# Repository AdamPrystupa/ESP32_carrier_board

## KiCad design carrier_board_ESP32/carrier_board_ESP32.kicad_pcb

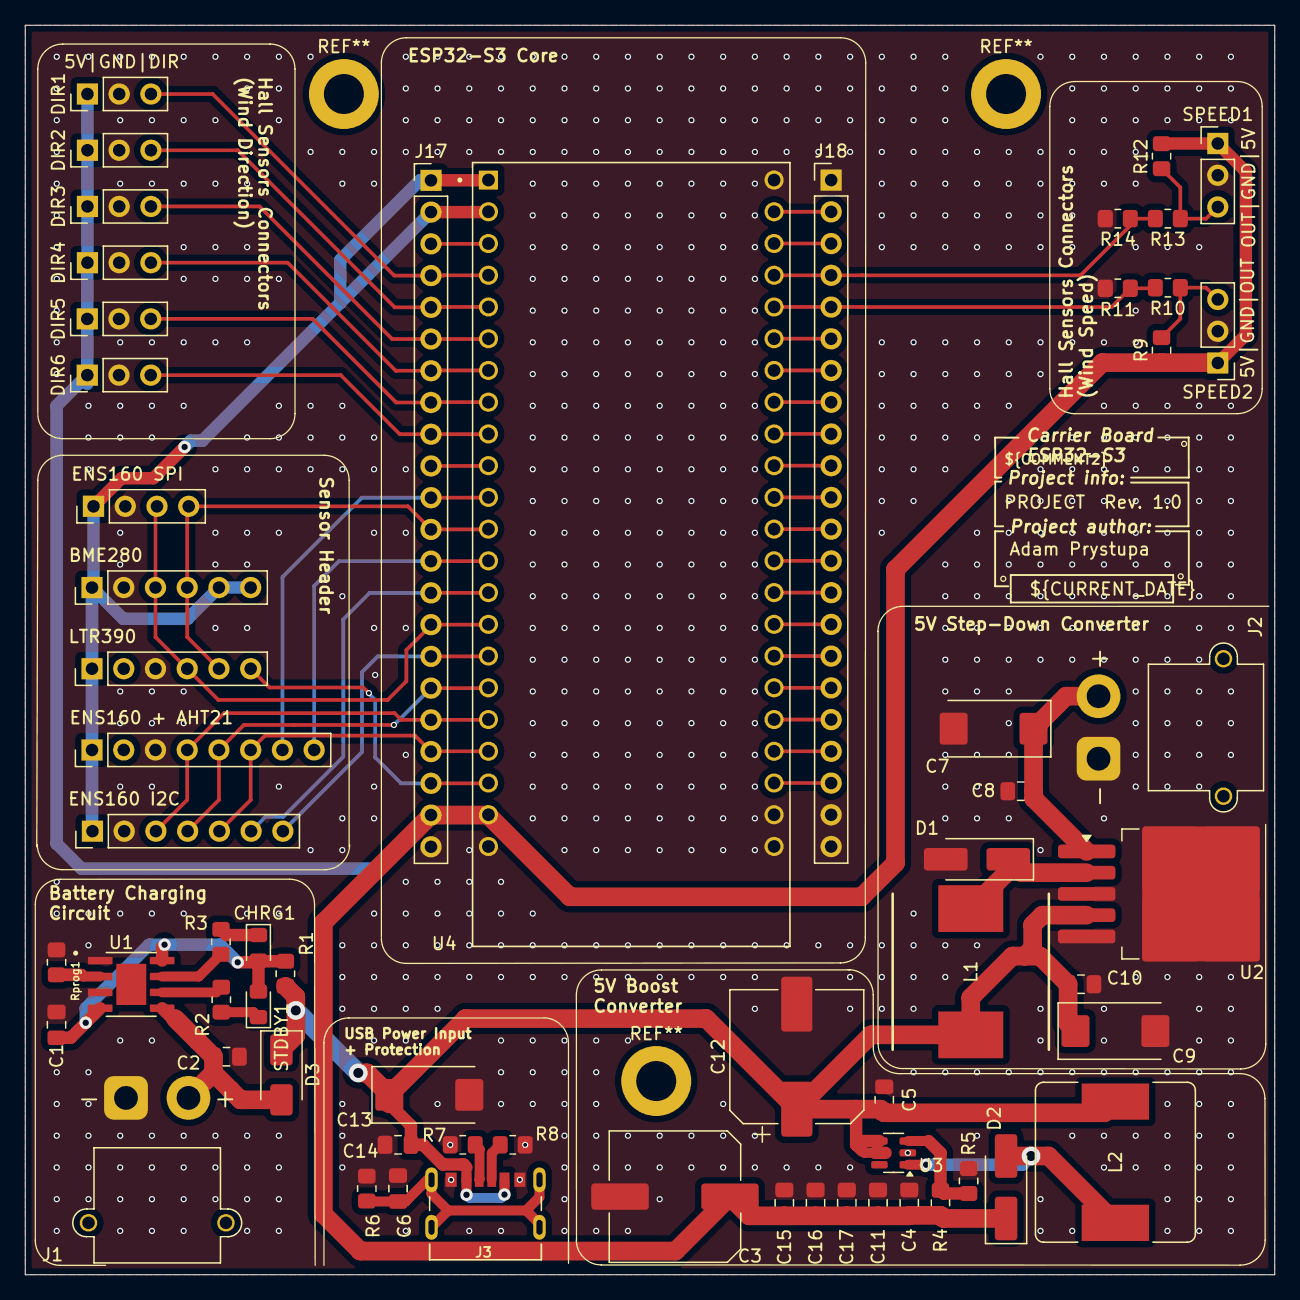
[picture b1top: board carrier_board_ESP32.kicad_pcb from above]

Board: 4 copper layers, 100.0 x 100.0 mm, 61 parts (0 on the bottom side), 57 nets.

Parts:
C1, C2, C8, C10, C15, C16, C17: 10uF; C_0805_2012Metric_Pad1.18x1.45mm_HandSolder
C3: 1000uF; C_Elec_10x10.2
C4, C5: 22nF; C_0805_2012Metric_Pad1.18x1.45mm_HandSolder
C6: 100nF; C_0805_2012Metric_Pad1.18x1.45mm_HandSolder
C7, C9: 100uF; CP_EIA-7343-15_Kemet-W_Pad2.25x2.55mm_HandSolder
C11: 47uF; C_0805_2012Metric_Pad1.18x1.45mm_HandSolder
C12: 2200uF; CP_Elec_10x10.5
C13: 10uF; CP_EIA-7343-15_Kemet-W_Pad2.25x2.55mm_HandSolder
C14: 1uF; C_0805_2012Metric_Pad1.18x1.45mm_HandSolder
CHRG1: RED; LED_0805_2012Metric_Pad1.15x1.40mm_HandSolder
D1, D2: DO-214AC; D_SMA_Handsoldering
D3: D; D_SMA
DIR1, DIR2, DIR3, DIR4, DIR5, DIR6: Conn_01x03_Socket; PinHeader_1x03_P2.54mm_Vertical
J1, J2: Conn_01x02_Socket; AMASS_XT30PW-M_1x02_P2.50mm_Horizontal
J3: UJC-HP-3-SMT-TR; CUI_UJC-HP-3-SMT-TR
J12: LTR390; PinHeader_1x06_P2.54mm_Vertical
J13: BME280; PinHeader_1x06_P2.54mm_Vertical
J14: ENS160 SPI; PinHeader_1x07_P2.54mm_Vertical
J15: ENS160 + AHT21; PinHeader_1x08_P2.54mm_Vertical
J16: ENS160 I2C; PinHeader_1x04_P2.54mm_Vertical
J17, J18: Conn_01x22_Socket; PinHeader_1x22_P2.54mm_Vertical
L1: 100uH; INDPM125125X800N
L2: 10uH; L_Bourns_SRR1260
R1: 0.4Ω; R_0805_2012Metric_Pad1.20x1.40mm_HandSolder
R2, R3, R10, R13: 1kΩ; R_0805_2012Metric_Pad1.20x1.40mm_HandSolder
R4: 110kΩ; R_0805_2012Metric_Pad1.20x1.40mm_HandSolder
R5: 15kΩ; R_0805_2012Metric_Pad1.20x1.40mm_HandSolder
R6: 330Ω; R_0805_2012Metric_Pad1.20x1.40mm_HandSolder
R7, R8: 5.1kΩ; R_0805_2012Metric_Pad1.20x1.40mm_HandSolder
R9, R12: 4k7Ω; R_0805_2012Metric_Pad1.20x1.40mm_HandSolder
R11, R14: 2kΩ; R_0805_2012Metric_Pad1.20x1.40mm_HandSolder
Rprog1: 1.2kΩ; R_0805_2012Metric_Pad1.20x1.40mm_HandSolder
SPEED1, SPEED2: Conn_01x03_Socket; PinHeader_1x03_P2.54mm_Vertical
STDBY1: GREEN; LED_0805_2012Metric_Pad1.15x1.40mm_HandSolder
U1: TP4056; SOP127P600X175-9N
U2: LM2576HVS-5; TO-263-5_TabPin3
U3: MT3608; SOT-23-6
U4: ESP32-S3-DEVKITC-1-N8R2; XCVR_ESP32-S3-DEVKITC-1-N8R2

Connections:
/3V3: J12.1, J13.1, J13.5, J13.6, J14.1, J15.1, J16.1, J17.1, J17.2, U4.J1_1 (3V3), U4.J1_2 (3V3)
/5V: C3.1, C4.1, C11.1, C15.1, C16.1, C17.1, D2.1 (K), DIR1.1, DIR2.1, DIR3.1, DIR4.1, DIR5.1, DIR6.1, J17.21, R4.1, R9.1, R12.1, SPEED1.1, SPEED2.1, U4.J1_21 (5V0)
/5V_supply: C5.1, C9.1, C10.1, C12.1, C13.1, C14.1, D3.1 (K), J3.A9 (V-BUS), J3.B9 (V-BUS), L1.2, L2.1, R1.1, U2.4 (FB), U3.4 (EN), U3.5 (IN)
/BATT+: C2.1, D3.2 (A), J1.2, U1.5 (BAT)
/CS_1: J15.7, J17.11, U4.J1_11 (GPIO18)
/CS_3: J14.6, J17.14, U4.J1_14 (GPIO46)
/DIR_1: DIR1.3, J17.4, U4.J1_4 (GPIO4)
/DIR_2: DIR2.3, J17.5, U4.J1_5 (GPIO5)
/DIR_3: DIR3.3, J17.6, U4.J1_6 (GPIO6)
/DIR_4: DIR4.3, J17.7, U4.J1_7 (GPIO7)
/DIR_5: DIR5.3, J17.8, U4.J1_8 (GPIO15)
/DIR_6: DIR6.3, J17.9, U4.J1_9 (GPIO16)
/GPIO0: J18.14, U4.J3_14 (GPIO0)
/GPIO17: J17.10, U4.J1_10 (GPIO17)
/GPIO19: J18.20, U4.J3_20 (USB_D-/GPIO19)
/GPIO20: J18.19, U4.J3_19 (USB_D+/GPIO20)
/GPIO21: J18.18, U4.J3_18 (GPIO21)
/GPIO35: J18.13, U4.J3_13 (GPIO35)
/GPIO36: J18.12, U4.J3_12 (GPIO36)
/GPIO37: J18.11, U4.J3_11 (GPIO37)
/GPIO38: J18.10, U4.J3_10 (GPIO38)
/GPIO39: J18.9, U4.J3_9 (MTCK/GPIO39)
/GPIO40: J18.8, U4.J3_8 (MTDO/GPIO40)
/GPIO41: J18.7, U4.J3_7 (MTDI/GPIO41)
/GPIO42: J18.6, U4.J3_6 (MTMS/GPIO42)
/GPIO45: J18.15, U4.J3_15 (GPIO45)
/GPIO47: J18.17, U4.J3_17 (GPIO47)
/GPIO48: J18.16, U4.J3_16 (GPIO48)
/INT_1: J15.8, J17.13, U4.J1_13 (GPIO3)
/INT_2: J12.6, J17.20, U4.J1_20 (GPIO14)
/INT_3: J14.7, J17.16, U4.J1_16 (GPIO10)
/MISO: J14.5, J15.6, J17.19, U4.J1_19 (GPIO13)
/MOSI: J14.4, J15.5, J17.17, U4.J1_17 (GPIO11)
/OUT1: R12.2, R13.1, SPEED1.3
/OUT2: R9.2, R10.1, SPEED2.3
/RST: J17.3, U4.J1_3 (RST)
/RX: J18.3, U4.J3_3 (U0RXD/GPIO44)
/SCK: J14.3, J15.4, J17.18, U4.J1_18 (GPIO12)
/SCL: J12.4, J13.3, J16.3, J17.15, U4.J1_15 (GPIO9)
/SDA: J12.5, J13.4, J16.4, J17.12, U4.J1_12 (GPIO8)
/SOLAR+: C7.1, C8.1, J2.2, U2.1 (VIN)
/SPEED_1: J18.4, R13.2, R14.1, U4.J3_4 (GPIO1)
/SPEED_2: J18.5, R10.2, R11.1, U4.J3_5 (GPIO2)
/TX: J18.2, U4.J3_2 (U0TXD/GPIO43)
GND: C1.2, C2.2, C3.2, C4.2, C5.2, C6.2, C7.2, C8.2, C9.2, C10.2, C11.2, C12.2, C13.2, C14.2, C15.2, C16.2, C17.2, D1.2 (A), DIR1.2, DIR2.2, DIR3.2, DIR4.2, DIR5.2, DIR6.2, J1.1, J2.1, J3.A12 (GND), J3.B12 (GND), J12.3, J13.2, J14.2, J15.3, J16.2, J17.22, J18.1, J18.21, J18.22, R5.2, R6.2, R7.2, R8.2, R11.2, R14.2, Rprog1.2, SPEED1.2, SPEED2.2, U1.1 (TEMP), U1.3 (GND), U2.3 (GND), U2.5 (~ON/OFF), U3.2 (GND), U4.J1_22 (GND), U4.J3_1 (GND), U4.J3_21 (GND), U4.J3_22 (GND)
unnamed: C6.1, J3.S1 (SHIELD), J3.S2 (SHIELD), J3.S3 (SHIELD), J3.S4 (SHIELD), R6.1
unnamed: C1.1, CHRG1.2 (A), R1.2, STDBY1.2 (A), U1.4 (VCC), U1.8 (CE)
unnamed: CHRG1.1 (K), R3.1
unnamed: D1.1 (K), L1.1, U2.2 (OUT)
unnamed: D2.2 (A), L2.2, U3.1 (SW)
unnamed: J3.A5 (CC1), R7.1
unnamed: J3.B5 (CC2), R8.1
unnamed: R2.1, STDBY1.1 (K)
unnamed: Rprog1.1, U1.2 (PROG)
unnamed: R3.2, U1.7 (~CHRG)
unnamed: R2.2, U1.6 (~STDBY)
unnamed: R4.2, R5.1, U3.3 (FB)

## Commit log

2025-03-23 parts list v1
2025-03-23 parts list - new ESP32 version
2025-03-23 begining of circuit design
2025-03-24 PCB designing
2025-03-30 added power supply (battery and solar panel)
2025-04-02 completed supply section
2025-04-02 added hall sensor for wind speed and direction mesuring
2025-04-02 completed escheme without rain detector
2025-04-10 formated file, ready for check
2025-05-13 pcb changes
2025-05-13 updated scheme and PCB ready for inspection
2025-05-13 Fixed errors, added mounting holes
2025-05-14 added step model of pcb
2025-05-21 Ready to fabrication
2025-06-26 cleaning repo
